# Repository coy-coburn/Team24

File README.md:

# Ground Breakers
####Ground Penetrating Radar Github

The goal of this project is to create a ground penetrating radar system to serve as a non-destructive method for mapping plant root systems. The system consists of a transmitting and receiving antenna and circuitry for both the transmitter and receiver. The transmitting circuit generates a linear frequency-modulated continuous wave from 2.415- 2.425GHz. The wave is pulsed to avoid interference between the transmitting and receiving antenna. The transmitting antenna passes the generated signal into the ground while the receiving antenna collects the reflected signal. The signal will reflect off materials with different dielectric constants like that of roots and pipes. The received signal will then be sent through an LNA for amplification to balance any loss of gain. The signal is also fed into a frequency mixer to correct any occured frequency shift. Finally, the IF signal is converted into digital data that will be recorded for image processing.

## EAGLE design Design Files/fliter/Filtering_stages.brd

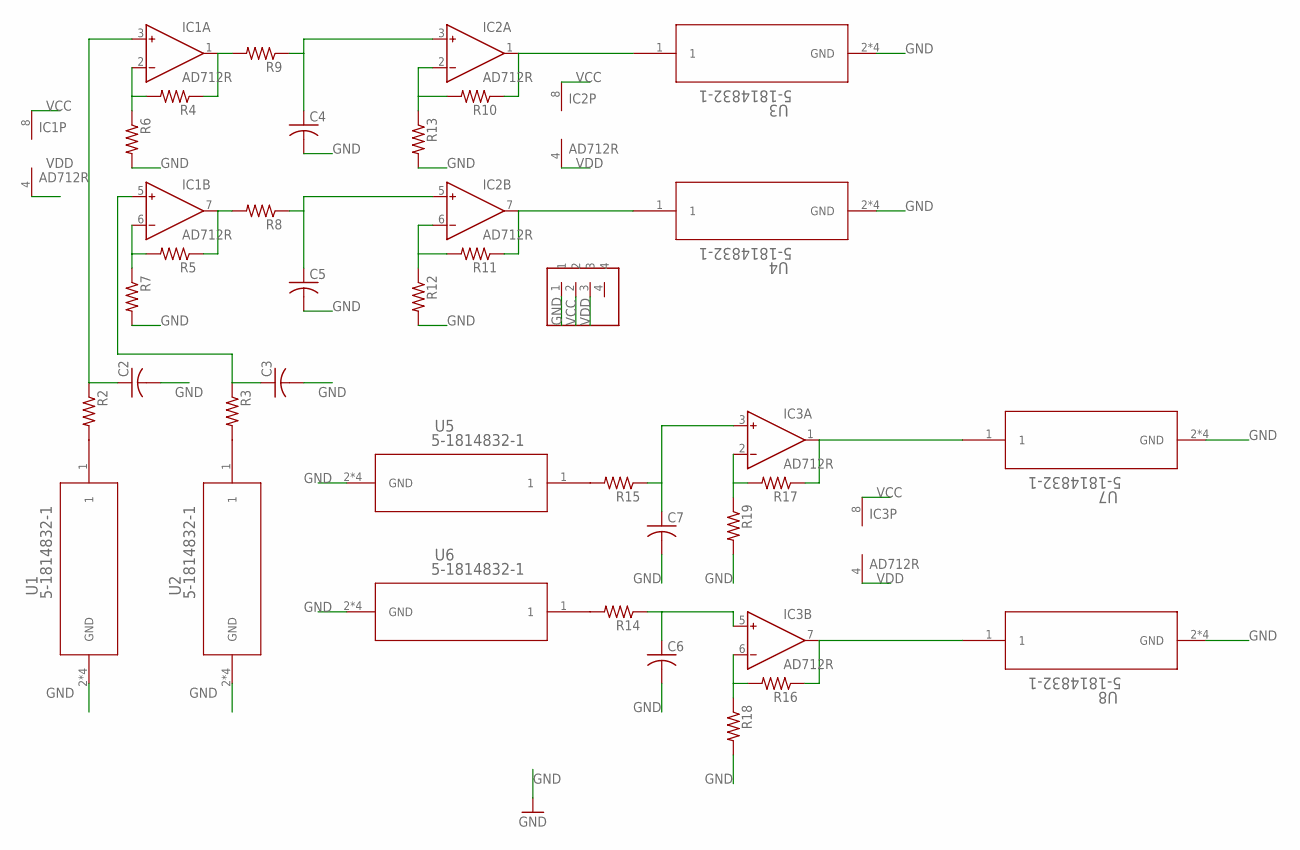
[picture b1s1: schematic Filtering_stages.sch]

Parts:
C2, C3, C4, C5, C6, C7: C-US025-025X050; C025-025X050
IC1, IC2, IC3: AD712R; SO8
R2, R3, R4, R5, R6, R7, R8, R9, R10, R11, R12, R13, R14, R15, R16, R17, R18, R19: R-US_0204/7; 0204/7
U1, U2, U3, U4, U5, U6, U7, U8: 5-1814832-1
U$1: ED2582-ND

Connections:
GND: C2.2, C3.2, C4.2, C5.2, C6.2, C7.2, R6.2, R7.2, R12.2, R13.2, R18.2, R19.2, U1.2 (GND), U1.3 (GND), U1.4 (GND), U1.5 (GND), U2.2 (GND), U2.3 (GND), U2.4 (GND), U2.5 (GND), U3.2 (GND), U3.3 (GND), U3.4 (GND), U3.5 (GND), U4.2 (GND), U4.3 (GND), U4.4 (GND), U4.5 (GND), U5.2 (GND), U5.3 (GND), U5.4 (GND), U5.5 (GND), U6.2 (GND), U6.3 (GND), U6.4 (GND), U6.5 (GND), U7.2 (GND), U7.3 (GND), U7.4 (GND), U7.5 (GND), U8.2 (GND), U8.3 (GND), U8.4 (GND), U8.5 (GND), U$1.1
unnamed: R2.2, U1.1
unnamed: R3.2, U2.1
unnamed: C2.1, IC1.3 (IN+), R2.1
unnamed: C3.1, IC1.5 (IN+), R3.1
unnamed: IC1.6 (IN-), R5.2, R7.1
unnamed: IC1.7 (OUT), R5.1, R8.2
unnamed: IC1.1 (OUT), R4.1, R9.2
unnamed: IC1.2 (IN-), R4.2, R6.1
unnamed: C4.1, IC2.3 (IN+), R9.1
unnamed: IC2.2 (IN-), R10.2, R13.1
unnamed: IC2.6 (IN-), R11.2, R12.1
unnamed: IC2.1 (OUT), R10.1, U3.1
unnamed: IC2.7 (OUT), R11.1, U4.1
unnamed: C5.1, IC2.5 (IN+), R8.1
unnamed: R14.2, U6.1
unnamed: R15.2, U5.1
unnamed: C7.1, IC3.3 (IN+), R15.1
unnamed: IC3.2 (IN-), R17.2, R19.1
unnamed: IC3.1 (OUT), R17.1, U7.1
unnamed: C6.1, IC3.5 (IN+), R14.1
unnamed: IC3.6 (IN-), R16.2, R18.1
unnamed: IC3.7 (OUT), R16.1, U8.1
VCC: IC1.8 (V+), IC2.8 (V+), IC3.8 (V+), U$1.2
VDD: IC1.4 (V-), IC2.4 (V-), IC3.4 (V-), U$1.3

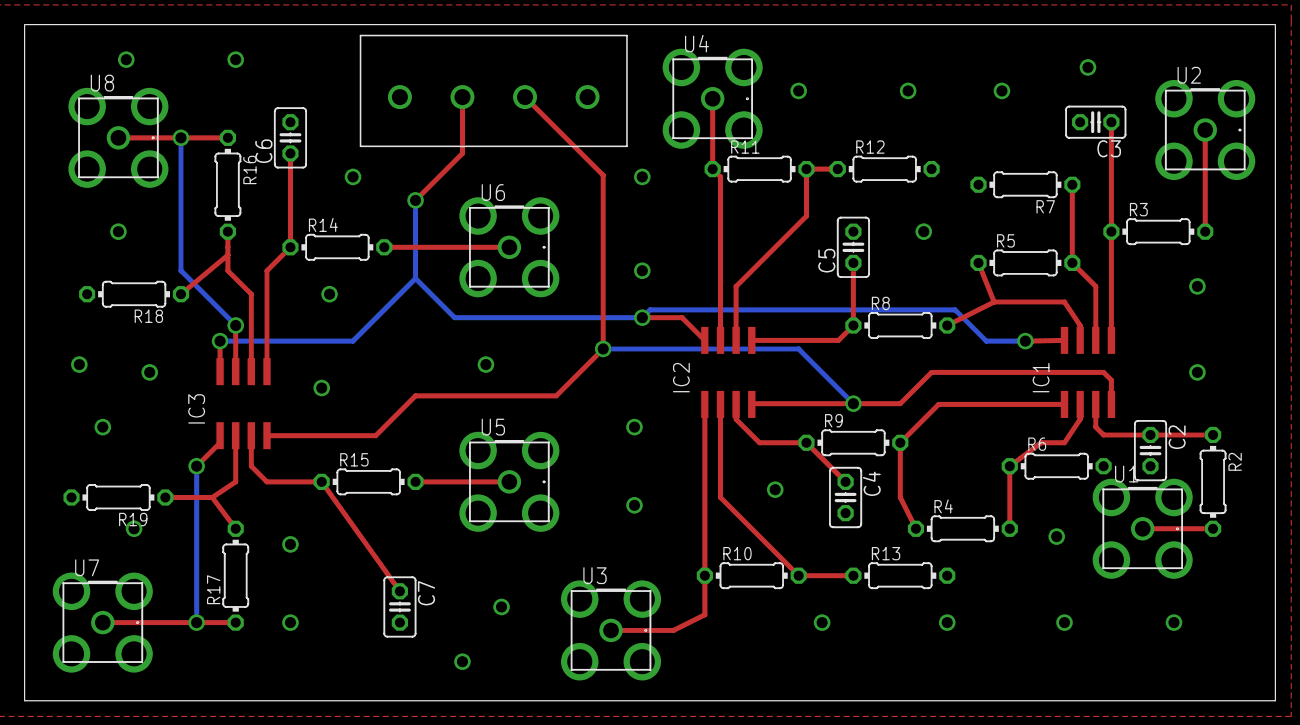
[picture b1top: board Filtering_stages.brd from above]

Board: 2 copper layers, 101.6 x 54.9 mm, 36 parts (0 on the bottom side), 25 nets.

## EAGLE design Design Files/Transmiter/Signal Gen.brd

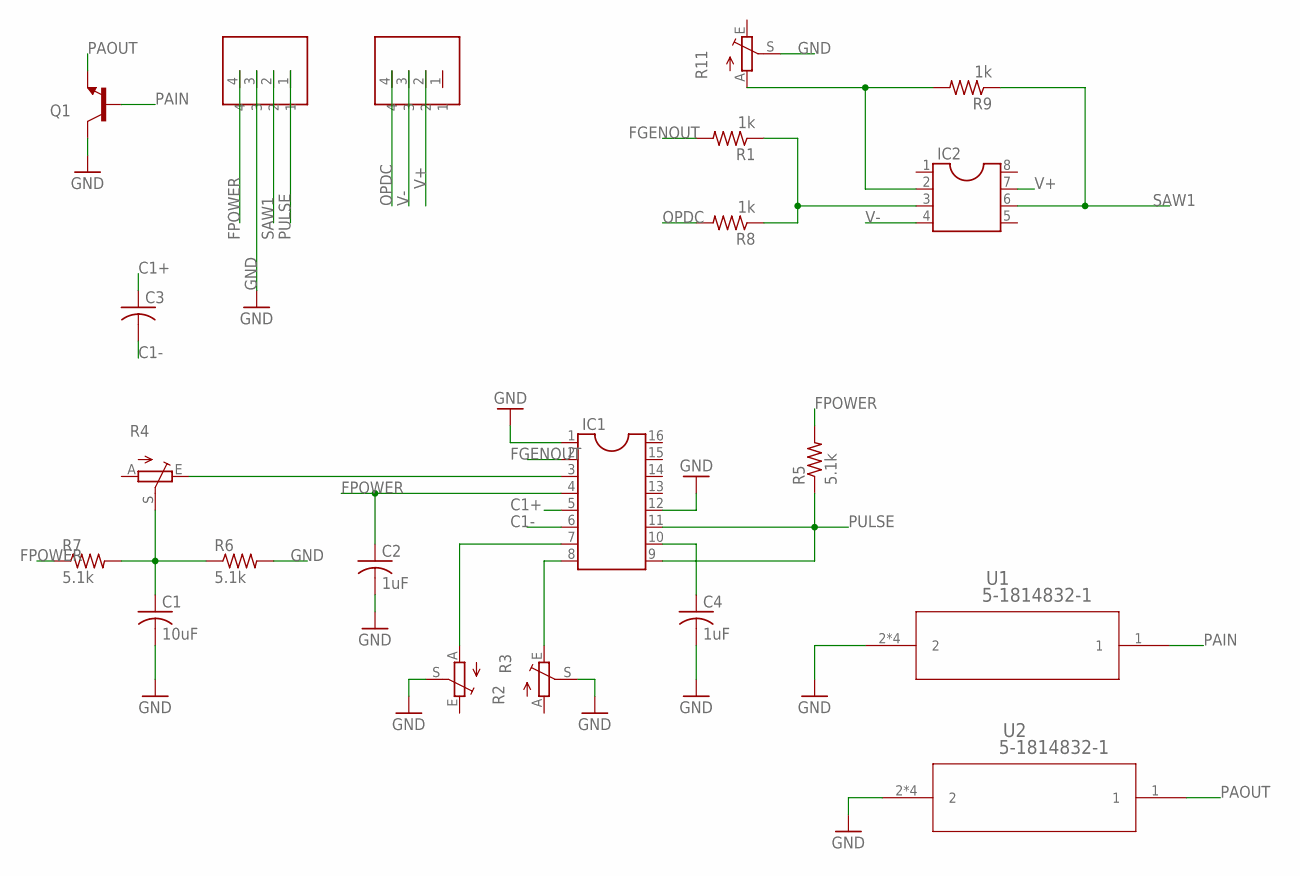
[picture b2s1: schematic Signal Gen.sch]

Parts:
C1: 10uF; C025-025X050
C2, C4: 1uF; C025-025X050
C3: C-US025-025X050; C025-025X050
IC1: DIL16S; SOCKET-16
IC2: DIL8S; SOCKET-08
Q1: TRANSISTOR_NPNSOT89; SOT89
R1, R8, R9: 1k; 0204/7
R2, R3: TRIM_EU-B25U; B25U
R4: TRIM_EU-B64W; B64W
R5, R6, R7: 5.1k; 0204/7
R11: TRIM_EU-RJ9W; RJ9W
U1, U2: 5-1814832-1
U$1, U$2: ED2582-ND

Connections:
C1+: C3.1, IC1.5
C1-: C3.2, IC1.6
FGENOUT: IC1.2, R1.2
FPOWER: C2.1, IC1.4, R5.2, R7.1, U$1.4
GND: C1.2, C2.2, C4.2, IC1.1, IC1.12, Q1.2 (C), R2.S, R3.S, R6.2, R11.S, U1.2, U1.3 (2), U1.4 (2), U1.5 (2), U2.2, U2.3 (2), U2.4 (2), U2.5 (2), U$1.3
unnamed: IC1.3, R4.E
unnamed: C1.1, R4.S, R6.1, R7.2
unnamed: IC1.7, R3.A
unnamed: IC1.8, R2.E
unnamed: C4.1, IC1.10
unnamed: IC2.3, R1.1, R8.1
unnamed: IC2.2, R9.2, R11.A
OPDC: R8.2, U$2.4
PAIN: Q1.1 (B), U1.1
PAOUT: Q1.3 (E), U2.1
PULSE: IC1.9, IC1.11, R5.1, U$1.1
SAW1: IC2.6, R9.1, U$1.2
V+: IC2.7, U$2.2
V-: IC2.4, U$2.3

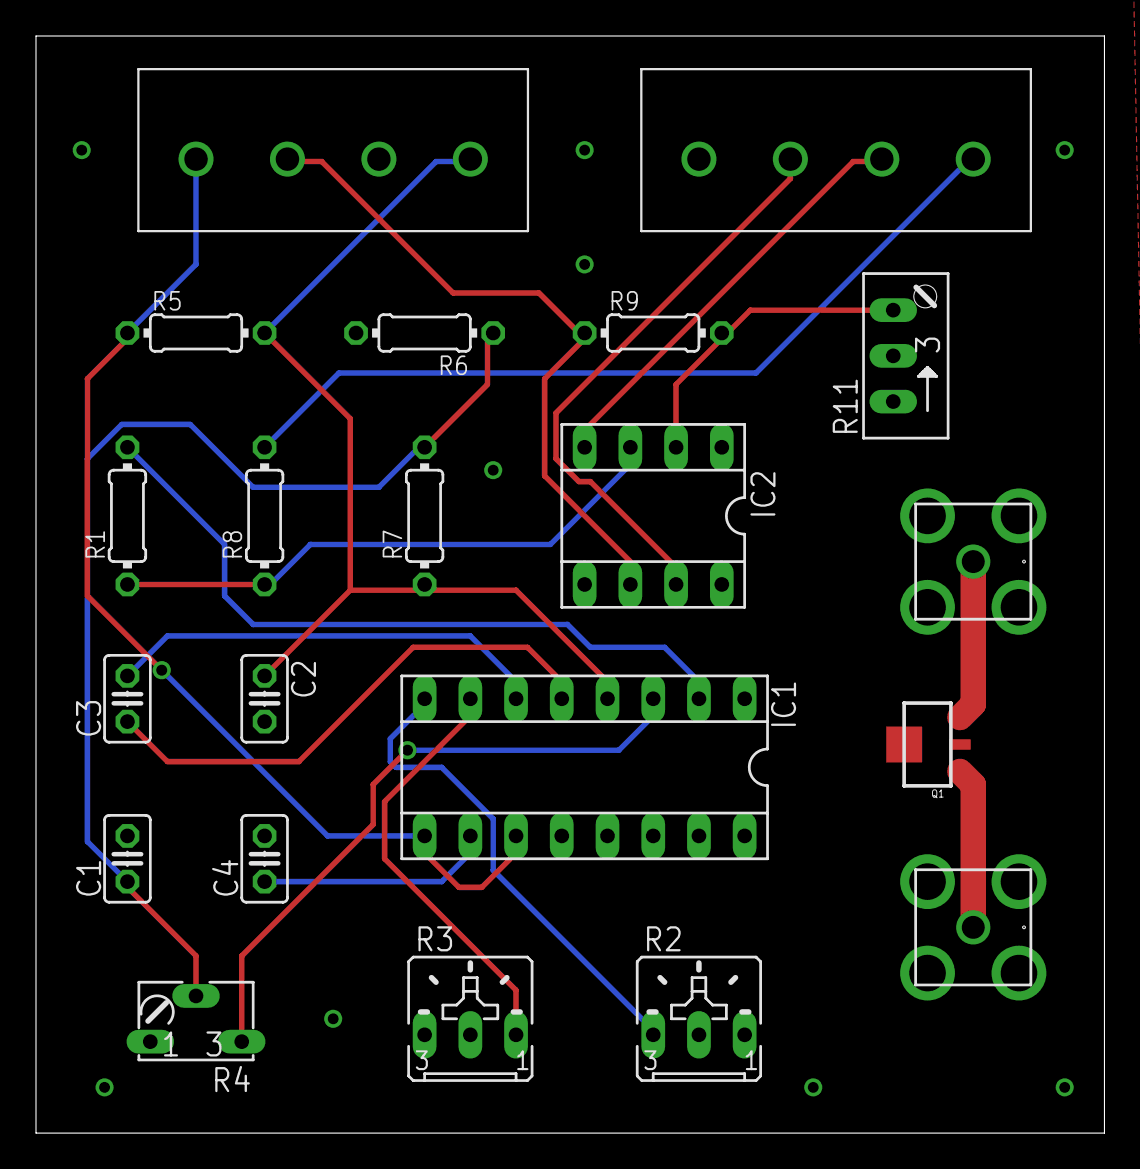
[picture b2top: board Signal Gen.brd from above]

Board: 2 copper layers, 59.4 x 61.0 mm, 21 parts (0 on the bottom side), 19 nets.

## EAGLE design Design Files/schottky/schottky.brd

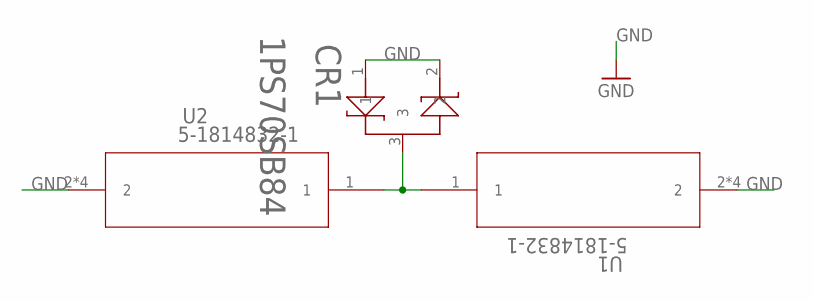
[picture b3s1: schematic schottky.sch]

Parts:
CR1: 1PS70SB84; SOT323
U1, U2: 5-1814832-1

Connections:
GND: CR1.1, CR1.2, U1.2, U1.3 (2), U1.4 (2), U1.5 (2), U2.2, U2.3 (2), U2.4 (2), U2.5 (2)
unnamed: CR1.3, U1.1, U2.1

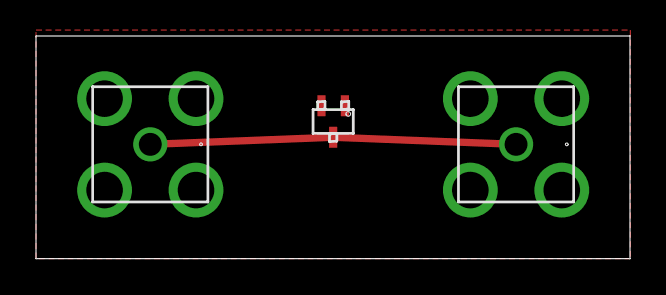
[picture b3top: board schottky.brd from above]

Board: 2 copper layers, 33.0 x 12.4 mm, 3 parts (0 on the bottom side), 2 nets.

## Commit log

2016-05-10 Team 24 - Design and research Files for GPR
2016-05-10 updated Read me

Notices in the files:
parts and their libraries:
SparkFun-DiscreteSemi: Licensing: Creative Commons ShareAlike 4.0 International - https://creativecommons.org/licenses/by-sa/4.0
COPYRIGHT: Copyright (C) 2015 Accelerated Designs. All rights reserved
